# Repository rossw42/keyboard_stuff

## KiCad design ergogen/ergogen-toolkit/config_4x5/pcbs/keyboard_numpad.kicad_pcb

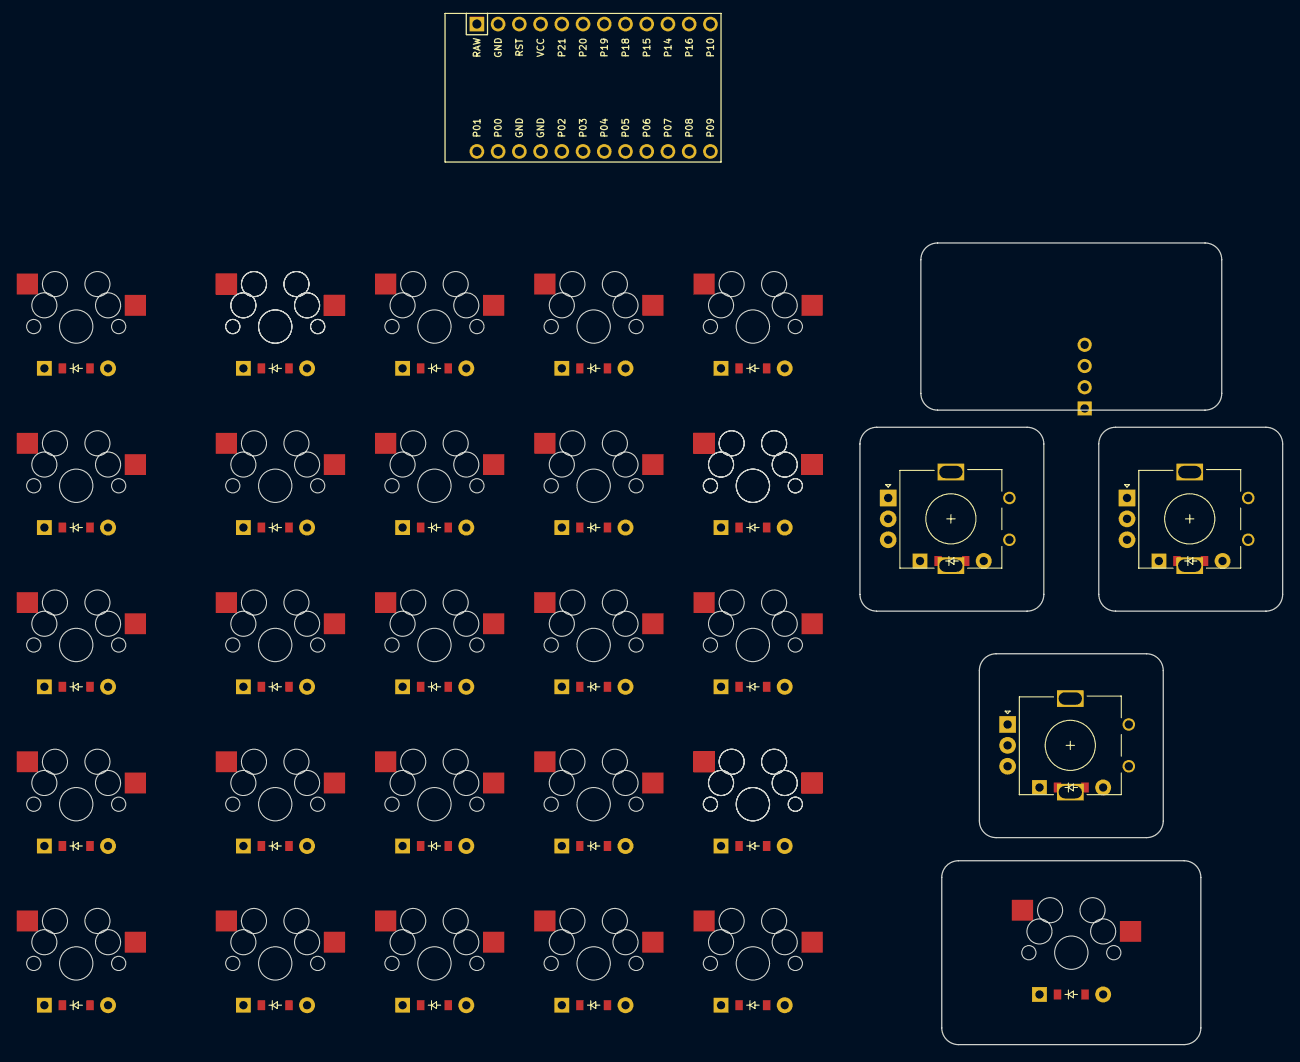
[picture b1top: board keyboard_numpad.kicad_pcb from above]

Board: 2 copper layers, 50.6 x 95.9 mm, 63 parts (0 on the bottom side), 46 nets, no tracks yet.

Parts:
D1, D2, D3, D4, D5, D6, D7, D8, D9, D10, D11, D12, D13, D14, D15, D16, D17, D18, D19, D20, D21, D22, D23, D24, D25, D26, D27, D28, D29: ComboDiode
MCU1: ProMicro
OLED1: OLED; OLED_headers
ROT1, ROT2, ROT3: rotary_encoder
S1, S2, S3, S4, S5, S6, S7, S8, S9, S10, S11, S12, S13, S14, S15, S16, S17, S18, S19, S20, S21, S22, S23, S24, S25, S26, S27, S28, S29: MX

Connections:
GND: MCU1.2, MCU1.15, MCU1.16, OLED1.1, ROT1.C, ROT2.C, ROT3.C
VCC: MCU1.4, OLED1.2
col0: MCU1.14, S1.1, S2.1, S3.1, S4.1, S5.1, S26.1
col0_row0: D1.2, S1.2
col0_row1: D2.2, S2.2
col0_row2: D3.2, S3.2
col0_row3: D4.2, S4.2
col0_row4: D5.2, S5.2
col1: MCU1.13, S6.1, S7.1, S8.1, S9.1, S10.1
col1_row0: D6.2, S6.2
col1_row1: D7.2, S7.2
col1_row2: D8.2, S8.2
col1_row3: D9.2, S9.2
col1_row4: D10.2, S10.2
col2: S11.1, S12.1, S13.1, S14.1, S15.1
col2_row0: D11.2, S11.2
col2_row1: D12.2, S12.2
col2_row2: D13.2, S13.2
col2_row3: D14.2, S14.2
col2_row4: D15.2, S15.2
col3: S16.1, S17.1, S18.1, S19.1, S20.1, S27.1, S28.1
col3_row0: D16.2, S16.2
col3_row1: D17.2, S17.2
col3_row2: D18.2, S18.2
col3_row3: D19.2, S19.2
col3_row4: D20.2, S20.2
col_enc_bottom: MCU1.24, ROT3.1
col_enc_left: MCU1.22, ROT1.1
col_enc_right: MCU1.23, ROT2.1
col_left: MCU1.20, S21.1, S22.1, S23.1, S24.1, S25.1
col_thumb: MCU1.19, S29.1
default_default: D26.2, D27.2, D28.2, D29.2
nav_col_row0: D21.2, S21.2
nav_col_row1: D22.2, S22.2
nav_col_row2: D23.2, S23.2
nav_col_row3: D24.2, S24.2
nav_col_row4: D25.2, S25.2
row0: D1.1, D6.1, D11.1, D16.1, D21.1, MCU1.12
row1: D2.1, D7.1, D12.1, D17.1, D22.1, MCU1.10, S27.2
row2: D3.1, D8.1, D13.1, D18.1, D23.1, MCU1.9
row3: D4.1, D9.1, D14.1, D19.1, D24.1, MCU1.11, S28.2
row4: D5.1, D10.1, D15.1, D20.1, D25.1, MCU1.5, S26.2
row_enc_bottom: D28.1, MCU1.6, ROT3.2
row_enc_left: D26.1, MCU1.8, ROT1.2
row_enc_right: D27.1, MCU1.7, ROT2.2
row_thumb: D29.1, MCU1.21, S29.2
